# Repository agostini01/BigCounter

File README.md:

BigCounter
==========
Arthur Benemann

Requesitos de Hardware:
- 4 displays de 7 segmentos
- 4 entradas para sinais externos
- 1 entrada para fonte de alimentação de 12v
- 4 furos para fixação
- placa 100x200mm

Requesitos de software:
- Contagem de pulsos de entrada externa, com debouncing.
- Reset da contagem com sinal externo
- Salvar a contagem na memoria ROM, para não perder a contagem quando faltar a luz
- Media dos ultimos valores

Workstation:
- Compilador XC08
- IDE MAPLAB X
- Eagle 6.1

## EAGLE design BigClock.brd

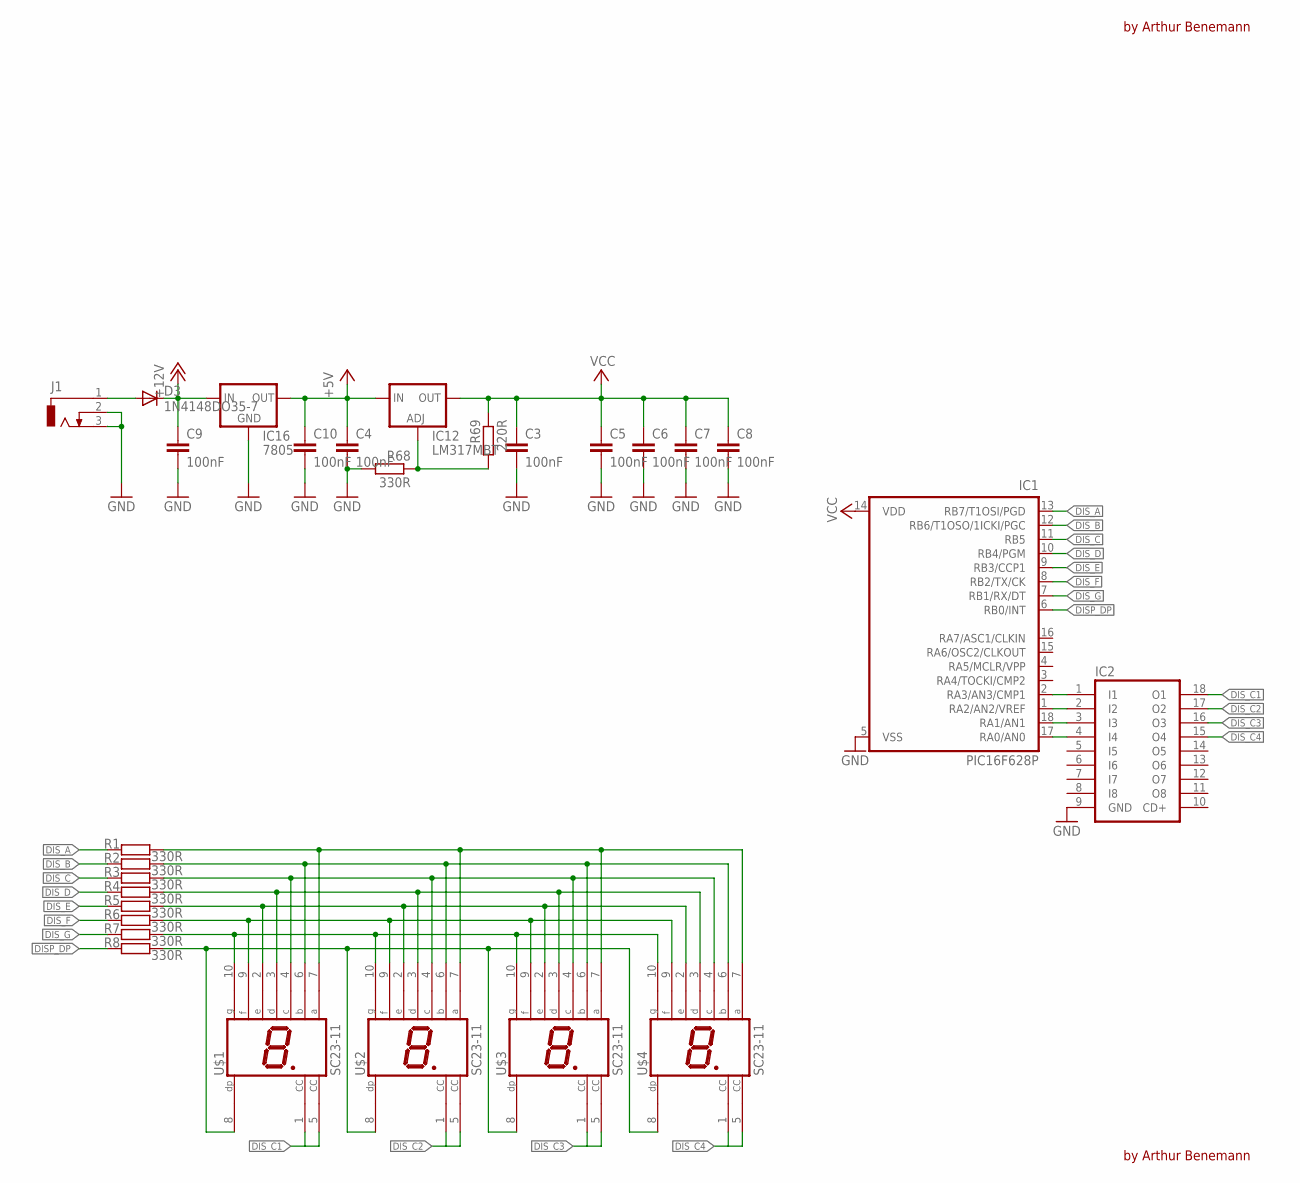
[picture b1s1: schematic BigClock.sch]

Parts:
C3, C4, C5, C6, C7, C8, C9, C10: 100nF; C050-025X075
D3: 1N4148DO35-7; DO35-7
IC1: PIC16F628P; DIL18
IC2: ULN2803A; DIL18
IC12: LM317MBT; TO220L1
IC16: 7805; 78XXL
J1: DCJ0303
R1, R2, R3, R4, R5, R6, R7, R8, R68: 330R; 0204/5
R69: 220R; 0204/5
U$1, U$2, U$3, U$4: SC23-11; SX23-XX

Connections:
+5V: C4.1, C10.1, IC12.3 (IN), IC16.OUT
+12V: C9.1, D3.C, IC16.IN
DISP_DP: IC1.6 (RB0/INT), R8.2
DIS_A: IC1.13 (RB7/T1OSI/PGD), R1.2
DIS_B: IC1.12 (RB6/T1OSO/1ICKI/PGC), R2.2
DIS_C: IC1.11 (RB5), R3.2
DIS_C1: IC2.18 (O1), U$1.1 (CC), U$1.5 (CC)
DIS_C2: IC2.17 (O2), U$2.1 (CC), U$2.5 (CC)
DIS_C3: IC2.16 (O3), U$3.1 (CC), U$3.5 (CC)
DIS_C4: IC2.15 (O4), U$4.1 (CC), U$4.5 (CC)
DIS_D: IC1.10 (RB4/PGM), R4.2
DIS_E: IC1.9 (RB3/CCP1), R5.2
DIS_F: IC1.8 (RB2/TX/CK), R6.2
DIS_G: IC1.7 (RB1/RX/DT), R7.2
GND: C3.2, C4.2, C5.2, C6.2, C7.2, C8.2, C9.2, C10.2, IC1.5 (VSS), IC2.9 (GND), IC16.GND, J1.2, J1.3, R68.2
unnamed: R8.1, U$1.8 (DP), U$2.8 (DP), U$3.8 (DP), U$4.8 (DP)
unnamed: IC1.2 (RA3/AN3/CMP1), IC2.1 (I1)
unnamed: IC1.1 (RA2/AN2/VREF), IC2.2 (I2)
unnamed: IC1.18 (RA1/AN1), IC2.3 (I3)
unnamed: IC1.17 (RA0/AN0), IC2.4 (I4)
unnamed: R7.1, U$1.10 (G), U$2.10 (G), U$3.10 (G), U$4.10 (G)
unnamed: R6.1, U$1.9 (F), U$2.9 (F), U$3.9 (F), U$4.9 (F)
unnamed: R5.1, U$1.2 (E), U$2.2 (E), U$3.2 (E), U$4.2 (E)
unnamed: R4.1, U$1.3 (D), U$2.3 (D), U$3.3 (D), U$4.3 (D)
unnamed: R3.1, U$1.4 (C), U$2.4 (C), U$3.4 (C), U$4.4 (C)
unnamed: R2.1, U$1.6 (B), U$2.6 (B), U$3.6 (B), U$4.6 (B)
unnamed: R1.1, U$1.7 (A), U$2.7 (A), U$3.7 (A), U$4.7 (A)
unnamed: D3.A, J1.1
unnamed: IC12.1 (ADJ), R68.1, R69.2
VCC: C3.1, C5.1, C6.1, C7.1, C8.1, IC1.14 (VDD), IC12.2 (OUT), R69.1

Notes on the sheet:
by Arthur Benemann

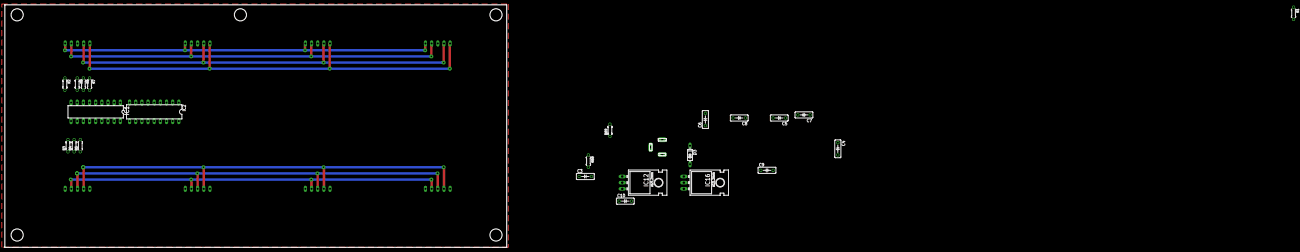
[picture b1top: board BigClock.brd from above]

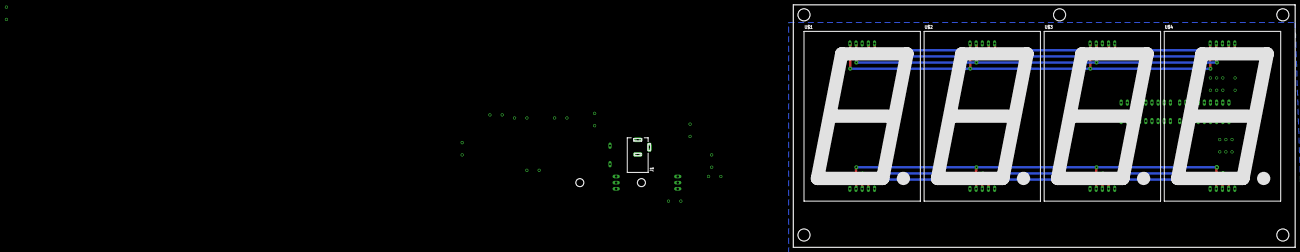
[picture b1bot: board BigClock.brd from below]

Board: 2 copper layers, 28 parts (5 on the bottom side), 30 nets.

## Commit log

2013-01-09 Adding files from 74Clock Project
2013-01-09 Cleaning-up the board from 74 clock project
2013-01-09 Adding the correct datasheet for the display
2013-01-09 Adicionando um modelo 3D para o projeto. Adicionando a biblioteca que contem os displays,
2013-01-09 Displays routed on schematics
2013-03-01 Modificações nas especificações
2013-03-01 Adicionando autor as especificações
2013-03-01 alteracoes no readme
2013-03-01 Adicionando info ao readme
2013-03-01 info para os requisitos
